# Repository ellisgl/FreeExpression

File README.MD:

# Open Source firmware replacement for Cricut(tm) Expression #

----------

**IMPORTANT: REPROGRAMMING THE CPU WILL PERMANENTLY ERASE YOUR ORIGINAL FIRMWARE THERE IS NO WAY TO GET THE ORIGINAL FIRMWARE BACK OTHER THAN BUYING ANOTHER MACHINE.** 

**About the Cricut** 
Cricut cutting machines can be had for about $50 or less on Craigslist. They contain two stepper motors, a moving solenoid powered knife holder that generates 12 volts to the solenoid using PWM.  They typically contain wheels that control speed, pressure, and other settings (one of them is usually an optical encoder, the others are potentiometers), a display of sorts, and a keyboard that has a ton of fairly useless buttons with green LED backlights.  Additionally, an onboard USB port and the Atmel ATMega1281 chip running at 16mhz provides all the horsepower you would need.  The stepper motors are controlled by eight mosfets.  So in reality, you get a fairly decent XY controller board with a PWM output for solenoid control.

*******************************************************************************
Original firmware cannot be copied from another machine (it has been locked and cannot be read from the CPU)

Original firmware cannot be restored through any PC application used for normal firmware upgrades.

This firmware has only been tested on the machine that I have. It may not work on your machine.  It may cause permanent damage, and it
will certainly void your warranty.

This firmware cannot read your original cartridges ever.

Cricut is a trademark of PROVO CRAFT and this firmware is **not** a PROVO CRAFT product. This firmware  was developed completely independently, without any documentation of PROVO CRAFT products, and without any and all original firmware. If you have problems with this firmware, do not consult PROVO CRAFT. 

Forked from https://github.com/thetazzbot/FreeExpression, which was was forked from https://github.com/Arlet/Freecut.

This will be aimed at the Expression V1 machine, and not the Cake or Personal machines. This code base is intended to be "clean" and be open source chain friendly.

## If you still want to proceed:
You will need a ATMEL programmer device, search for "ATMEL 51 AVR USB ISP ASP Microcontroller Programmer". And if you don't want to open the machine, you might want to get one of these adapters built: https://github.com/ellisgl/FreeExpression/tree/main/CricuitISPCartridge (I have a couple of these, and would be willing to part with my extras)

### Building: ##
```bash
sudo apt install gcc-avr avr-libc avrdude make cmake`  # For Debian/Ubuntu based systems

git clone https://github.com/ellisgl/FreeExpression
cd FreeExpression\build
cmake .. 
cmake --build .
make
```
### Burning: ##
```bash
avrdude -c usbasp -p m1281 -U flash:w:FreeExpression.hex
```

### Using
Use Inkscape to draw and send a file to the cutter.  Inkscape 0.91 has an export to Plot feature (under Extensions) which sends a HPGL langauge file to the COM port where the cutter is connected to. Use 9600 baud and  make sure XON/XOFF is selected for flow control. Inkscape works good on Windows and Linux machines.

----------
## Keypad key functions: ##

- On/Off: Powers the machine and executes carriage homing sequence.
- Move buttons: Moves the carriage and the media freely.
- Home (ResetAll): Re-homes the carriage, media is assumed to be unloaded.
- Load Paper: Pulls in media or cutting mat about 1/2".
- Unload Paper: Moves the mat/media back to the loading point. 
- X,Y Offset (BackSpace): Sets the current X and Y position as location 0,0 for following cuts
- Cutter Down (Numeral 1): Drops the cutter down. This only works when the media is loaded. Useful  for measuring actual cutting force with a scale.
- Cutter Up (Numeral 2): Moves the cutter away from the media.
- Cutting Speed	(Xtra2): In conjunction with the +/keys the cutting speed can be chosen in 9 steps.
- Cutting Pressure (Xtra1) : In conjunction with the +/keys the cutting pressure can be adjusted in 9 steps.
- Stop: Aborts the currently cached cutting operations, but new data arriving from the PC will still trigger subsequent motion.

## Dials ##
- Dial Speed: 	Also adjusts the cutting speed and is used to read the cutting speed after power up. Only the mid range of the speed choices can be selected, use the +/keys to get all the way to the end.
- Dial Pressure: Also adjusts the cutting pressure and is used to read the initial pressure on power-up. Only the mid range of the pressure choices can be selected, use the +/keys for the full range.
- Dial Size:  Not used. The machine can cut up to 80"x12"wide.

## Multi-cut and media lock ##
After the machine moves the media/carriage there is a time of about 1 minute (depending on speed setting) where the motors stay engaged and you can not move the media/carriage by hand. After this timeout the motors go into standby and you can move carriage and media by hand. This timeout is useful so that one can cut the same shape multiple times and not loose registration - for thick material multi-cut.

# Command language #
Currently supports HPGL -- HP Graphic Language. Cutting speed and pressure is NOT taken from the language input, only from keyboard and associated dials.

After the machine moves the media/carriage there is a time of about 1 minute at speed 5 where the motors stay engaged and you can not move the media/carriage by hand. After this timeout the motors go into standby and you can move carriage and media by hand. This timeout is useful so that one can cut the same shape multiple times and not loose registration - for thick material multi-cut.

# CAD and Cutting #
From the CAD system export via DXF format, then open that file in Inkscape. On the input dialog choose manual scale factor of 25.4 if the original CAD file was done in inch scale, otherwise set to 1.0. 
To cut, select all objects then use PATH/Object to Path, the Extensions/Export/Plot.  Plotter resolution set to 400 dpi.  Pen number, force and speed are ignored. Rotation and Mirror as desired. 
Connection Settings are 9600/XON/XOFF and HPGL for language. Com port number as per device manger. To execute press Apply.

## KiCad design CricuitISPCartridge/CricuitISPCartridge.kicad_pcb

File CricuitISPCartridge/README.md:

# Cricut ISP Cartridge

PCB to allow you to Connect to the ISP of the Atmega 1291 on the Cricut Expression / Personal and flash a free firmware like: FreeExpression https://hackaday.io/project/6331-freeexpression, with out having open the machine. This uses the 6 pin (2x3 2.54mm (0.1 inch) connector header.

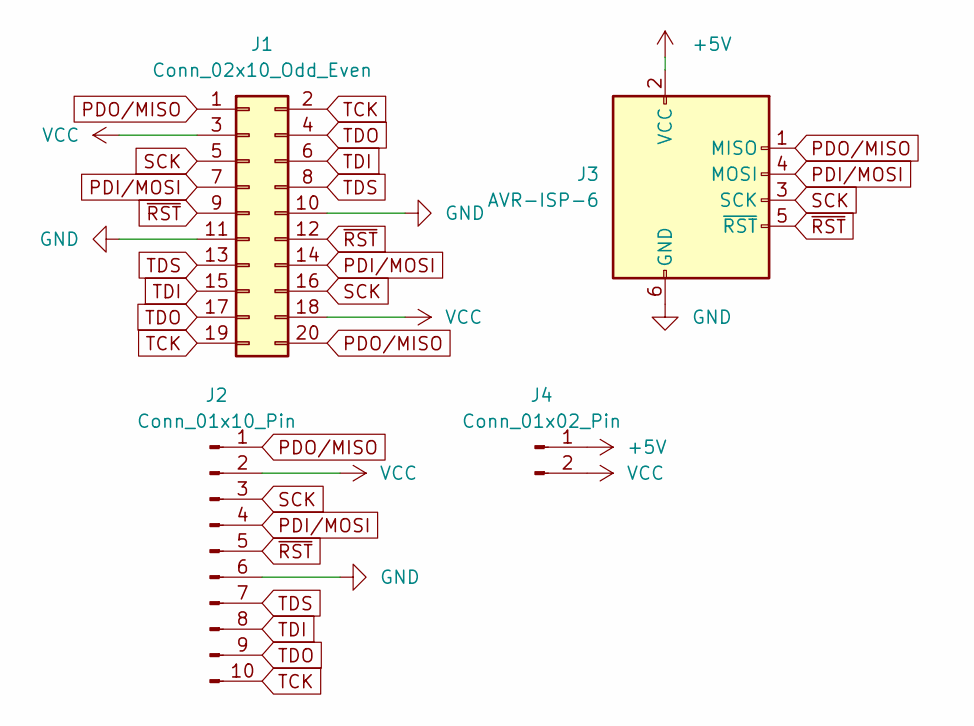
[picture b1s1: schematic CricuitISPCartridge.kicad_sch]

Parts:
J1: Conn_02x10_Odd_Even; 2x10
J2: Conn_01x10_Pin; PinHeader_1x10_P2.54mm_Vertical
J3: AVR-ISP-6; PinHeader_2x03_P2.54mm_Vertical
J4: Conn_01x02_Pin; PinHeader_1x02_P2.54mm_Vertical

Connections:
+5V: J3.2 (VCC), J4.1
GND: J1.10, J1.11, J2.6, J3.6 (GND)
PDI/MOSI: J1.7, J1.14, J2.4, J3.4 (MOSI)
PDO/MISO: J1.1, J1.20, J2.1, J3.1 (MISO)
SCK: J1.5, J1.16, J2.3, J3.3 (SCK)
TCK: J1.2, J1.19, J2.10
TDI: J1.6, J1.15, J2.8
TDO: J1.4, J1.17, J2.9
TDS: J1.8, J1.13, J2.7
VCC: J1.3, J1.18, J2.2, J4.2
~RST: J1.9, J1.12, J2.5, J3.5 (~RST)

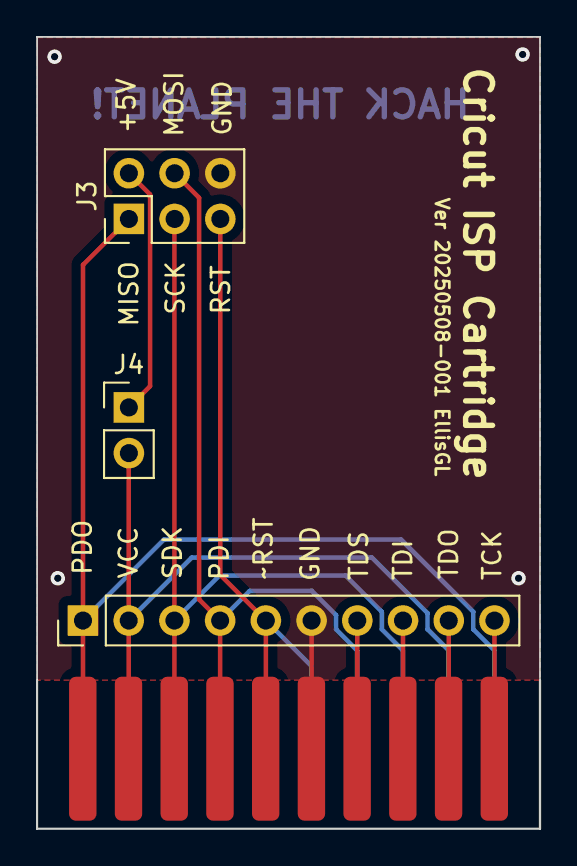
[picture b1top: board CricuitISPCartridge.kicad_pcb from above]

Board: 2 copper layers, 27.9 x 44.0 mm, 4 parts (0 on the bottom side), 11 nets.

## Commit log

2022-08-25 The cake was a lie. Removed all the Cake refrences and make the make files work!
2022-08-25 Updated make file to use the USBASP (cheap programmer)
2022-08-25 Cleanup.
2022-08-25 Changed targed to 'freeexpression' instead of 'freecut' in the Makefile. Also did a little of style cleanup in the Makefile.
2022-08-25 Applying my highly opinionated formatting style.
2022-08-25 Show version on the display.
2022-08-25 removing uneeded things.
2022-08-26 Moved document files into /docs. Redid Netbeans project config.
2022-08-26 Updated README.MD to more specific to this code base.
2022-08-26 Removed the other IDE / Toolchain stuff that wasn't Netbeans.
2022-08-26 Removed duplicated README.MD
2022-08-26 Make sure the GCC AVR build chain is selected in the NB config...
2022-08-26 Applied Formatting.
2022-08-26 Removed G-CODE and GPGL references. Closed #1
2022-08-26 Preincrement when possible. Closes #3
2023-01-10 Update README.MD
    Adding some building and flashing instructions.
2025-04-05 Create Makefile
    Moving this so I can run workflows.
2025-04-05 Update Makefile
2025-04-05 Fixing compliation issues
2025-04-05 Fix compliation issues
2025-04-05 Compile m2u8 first, then the main project?
2025-04-05 Revert "Fix compliation issues"
    This reverts commit 08056bbdf1360640dff7a5167a88c32b7815cd40.
2025-04-05 Revert "Compile m2u8 first, then the main project?"
    This reverts commit de5b4da93e53a202d3b181357e97293e777543af.
2025-04-05 Revert "Fix compliation issues"
    This reverts commit 0459b22ae2c87495def8b122d803ad2018d123cf.
2025-04-05 Revert "Fix compliation issues"
    This reverts commit c40b82d704f789d6d9410851b6c61ad3732e5c17.
2025-04-05 Revert "Fix compliation issues"
    This reverts commit 261ff6e1dbc0ab6e2d1c772c07eb05b9400146a0.
2025-04-05 Revert "Fixing compliation issues"
    This reverts commit e3c36e90b408ae835a6fcbc03b372074a9b8c798.
2025-04-05 Revert "Create keys.h"
    This reverts commit 51369334b752e349f64975cfa152f36cba7efc47.
2025-04-05 Revert "Update Makefile"
    This reverts commit e4dfb6176de6544358c56a4b1f42e5ba6462955a.
2025-04-05 Revert "Update Makefile"
    This reverts commit 4eca48911a8e1fb71beb40f997e65cba3ac025ea.
2025-04-05 Revert "Update Makefile"
    This reverts commit 6832a80236c587cb3c6778ee9efd891ef7f79a72.
2025-04-05 Revert "Update Makefile"
    This reverts commit 294336360c9ae9da4e2c22690e22270815c36753.
2025-04-05 Revert "Create c-cpp.yml"
    This reverts commit 1188233d4d1bdea1b5b463d3aeadd297fde558ff.
2025-04-05 Revert "Update Makefile"
    This reverts commit ee8a06fa9c7dabc95830f0c49e06b8f812f8faf2.
2025-04-05 Revert "Update Makefile"
    This reverts commit 93785dbeca10ffeb5d2f6bcc2c88070c26b912c8.
2025-04-05 Revert "Update README.MD"
    This reverts commit 56bc4995ac26e7ca7303791bac1491eaa05f053f.
2025-04-05 Revert "Create Makefile"
    This reverts commit fecce1f97441649f6d61ba221777f4c7650b5353.
2025-04-05 Let's use CMAKE instead.
2025-04-05 Remove nbproject.
2025-04-05 OCD capitalization in the base directory.
2025-04-05 Doc updates
2025-04-05 Styling?
2025-04-05 Adding the Cricuit ISP Programmer Cartrige KiCad stuff here
2025-04-05 Roudning the traces. Thank you new KiCad!
2025-04-05 Might as well add 3d renders.
2025-04-05 Update README.MD
    https://github.com/ellisgl/FreeExpression/tree/main/CricuitISPCartridge linked
2025-05-07 Updated the ISP addapter card PCB. Now with 100% more visable labeling
2025-05-08 Using modern web document tools
2025-05-08 Might as well break out all the ports for the cartridge slot.
